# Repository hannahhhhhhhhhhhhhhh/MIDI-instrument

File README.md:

# MIDI-instrument!
Inspired by a standard gamepad, anyone interested in music production can pick this MIDI instrument up without already knowing how to play an instrument. If someone 
can already play piano, they probably have access to a piano...
Soo this is for everyone else.

## Why I Made This
The design of this instrument is inspired by standard controller controls rather than shaped to mirror a certain instrument because it is for people who do not have a musical instrument, and more generally people who are interested in music production. Me and my friend often produce music together and sometimes what we find annoying is that we need a whole keyboard or a digital drum set MIDI inputs, specific MIDI guitars, etc, which is why I want my controls to be more universal rather than targeting one single instrument. It is also annoying switching from MIDI instruments to mouse then to keyboard when producing music, so I made the arrow controls easier to navigate between UIs.

## How It Works
The controller is built around the XIAO ESP32-S3 microcontroller, which reads all inputs and sends MIDI signals to a DAW over USB. The board has 7 main key switches arranged in a controller layout (t1-t7), 3 additional push buttons along the top (SW2, SW3, SW4), and 8 SK6812MINI-E addressable RGB LEDs chained in series for visual feedback. The LEDs are driven from the ESP32-S3 GPIO8 data line and powered at 3.3V. The key switches connect through a 7-pin connector (J1) back to the GPIO pins on the MCU.

### Control Layout
The up and down arrows would be for octave switching, while left and right arrows are for semitones, and the middle button is selecting/confirm the notes(t1-5). The two keys on the left of the arrow controls are for more detailed settings. The top left(t6) is for switching the mode to selecting note length(which will correspond to X key on the software), where then the up/right arrow would be lengthen the note and down/left would be shorten. 
The bottom left(t7) is mapped to the 'g' key on my computer which is the shortcut for me on vital studio to change the effect curve shape. The 3 switches on the top could be mapped to any 3 keyboard shortcut as well, for now I have it on 'e', 'esc', and 'r'.
The two rows of LEDs on the right side of the board serve as a stats display, showing feedback for the current mode or selection.

## Schematic

## PCB Layout

## Firmware Flashing Guide

### What You Need
- Arduino IDE 
- ESP32 board package installed
- USB-C cable

### Installing the ESP32 Board Package
1. Open Arduino IDE
4. Go to Tools > Board > Boards Manager
5. Search "esp32" and install the package by Espressif Systems

### Connecting the Board
1. Plug the XIAO ESP32-S3 into your computer via USB-C
2. Wait for drivers to install
3. If the port does not appear, download the CH343 driver from 
   seeedstudio.com

### Selecting the Board
1. Go to Tools > Board > esp32 > XIAO_ESP32S3
2. Go to Tools > Port and select the port that appeared when 
   you plugged in the board

### Uploading
1. Open `keyboard.ino` in Arduino IDE
2. Click the Upload button (right arrow, top left)
3. Wait for "Done uploading" in the console
4. The controller is ready to use

## Bill of Materials

| Item | Qty | Supplier | Cost/Item (CAD) | Total Cost (CAD) |
|------|-----|----------|-----------------|------------------|
| XIAO ESP32-S3 | 1 | Seeed Studio | $7.49 | $7.49 |
| SW_Push Button | 1 | YUNZII | $12.99 | $12.99 |
| Conn_01x07 7-pin Header | 1 | Seeed Studio | $0.64 | $0.64 |
| PCB Fabrication (JLCPCB) | 1 | JLCPCB | $9.40 | $9.40 |
| Estimated Shipping | 1 | — | — | $2.00 |
| | | | **Total** | **$32.52** |

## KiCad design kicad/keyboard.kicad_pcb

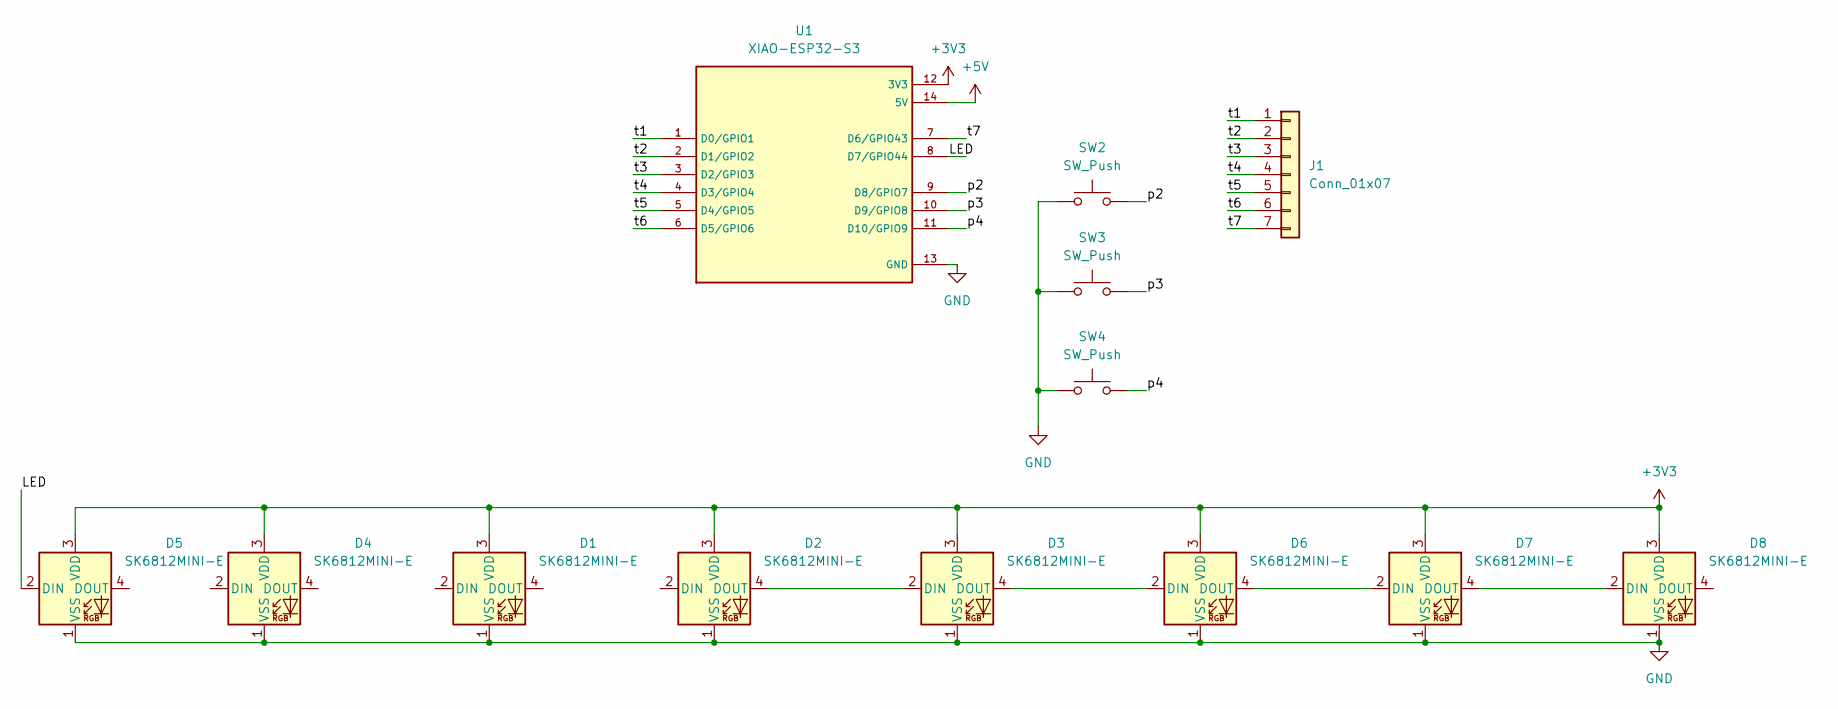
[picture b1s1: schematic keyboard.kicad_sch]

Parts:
D1, D2, D3, D4, D5, D6, D7, D8: SK6812MINI-E; LED_SK6812MINI-E_3.2x2.8mm_P1.5mm_ReverseMount
J1: Conn_01x07; padd
SW2, SW3, SW4: SW_Push; Kailh Choc Low-Profile Switches
U1: XIAO-ESP32-S3; XIAO ESP32-S3; PARTREV April 22nd, 2026

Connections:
+3V3: D1.3 (VDD), D2.3 (VDD), D3.3 (VDD), D4.3 (VDD), D5.3 (VDD), D6.3 (VDD), D7.3 (VDD), D8.3 (VDD), U1.12 (3V3)
+5V: U1.14 (5V)
/LED: D5.2 (DIN), U1.8 (D7/GPIO44)
/p2: SW2.2, U1.9 (D8/GPIO7)
/p3: SW3.2, U1.10 (D9/GPIO8)
/p4: SW4.2, U1.11 (D10/GPIO9)
/t1: J1.1, U1.1 (D0/GPIO1)
/t2: J1.2, U1.2 (D1/GPIO2)
/t3: J1.3, U1.3 (D2/GPIO3)
/t4: J1.4, U1.4 (D3/GPIO4)
/t5: J1.5, U1.5 (D4/GPIO5)
/t6: J1.6, U1.6 (D5/GPIO6)
/t7: J1.7, U1.7 (D6/GPIO43)
GND: D1.1 (VSS), D2.1 (VSS), D3.1 (VSS), D4.1 (VSS), D5.1 (VSS), D6.1 (VSS), D7.1 (VSS), D8.1 (VSS), SW2.1, SW3.1, SW4.1, U1.13 (GND)
unnamed: D2.4 (DOUT), D3.2 (DIN)
unnamed: D3.4 (DOUT), D6.2 (DIN)
unnamed: D6.4 (DOUT), D7.2 (DIN)
unnamed: D7.4 (DOUT), D8.2 (DIN)

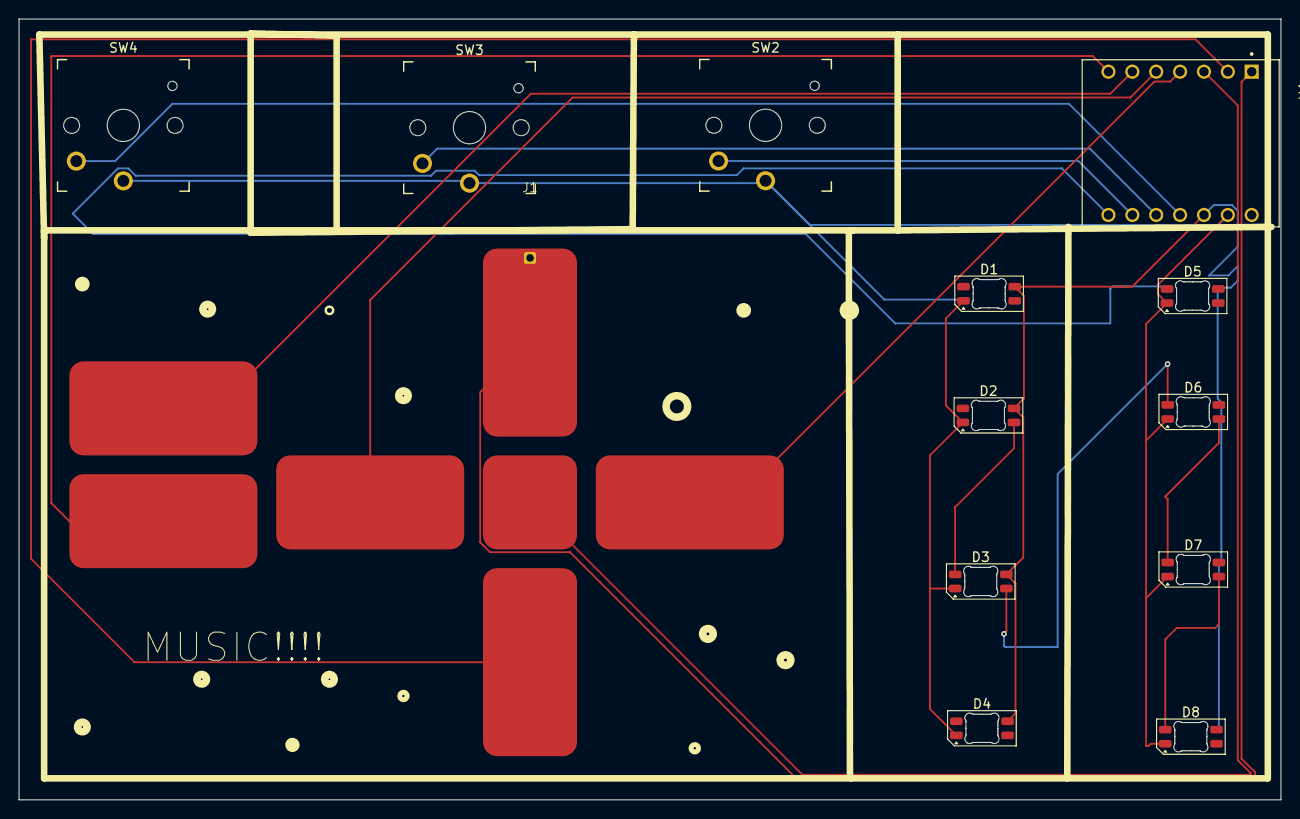
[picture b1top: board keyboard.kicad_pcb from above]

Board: 2 copper layers, 134.2 x 83.1 mm, 13 parts (0 on the bottom side), 17 nets.

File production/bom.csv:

Designator,Footprint,Quantity,Value,LCSC Part #
"D1, D2, D3, D4, D5, D6, D7, D8",LED_SK6812MINI-E_3.2x2.8mm_P1.5mm_ReverseMount,8,SK6812MINI-E,
J1,padd,1,Conn_01x07,
"SW2, SW3, SW4",Kailh Choc Low-Profile Switches,3,SW_Push,
U1,XIAO ESP32-S3,1,XIAO-ESP32-S3,
